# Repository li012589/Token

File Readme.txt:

Welcome to JRT token project!!

			   This is a readme file

				Ver. Alpha

		   ***************************************

For eagle schematic and borad files go to Hardware, schematic files are ended with .sch while borad files are ended with .brd 
For hardware document, go to /Hardware/document

For software, go to /Software
For information (e.g. todo list) about software, go to /Software/document

Enjoy your day!

		   ****************************************

Known Bugs:

		   ****************************************
Hosted By Li S.H.@li012589li@163.com  
	  Lv Y.X.@376324017@qq.com

locate at JinLin Univ. robot team Jinlin University,South QianWei ChangChun 	  	          Jilin Prov. China

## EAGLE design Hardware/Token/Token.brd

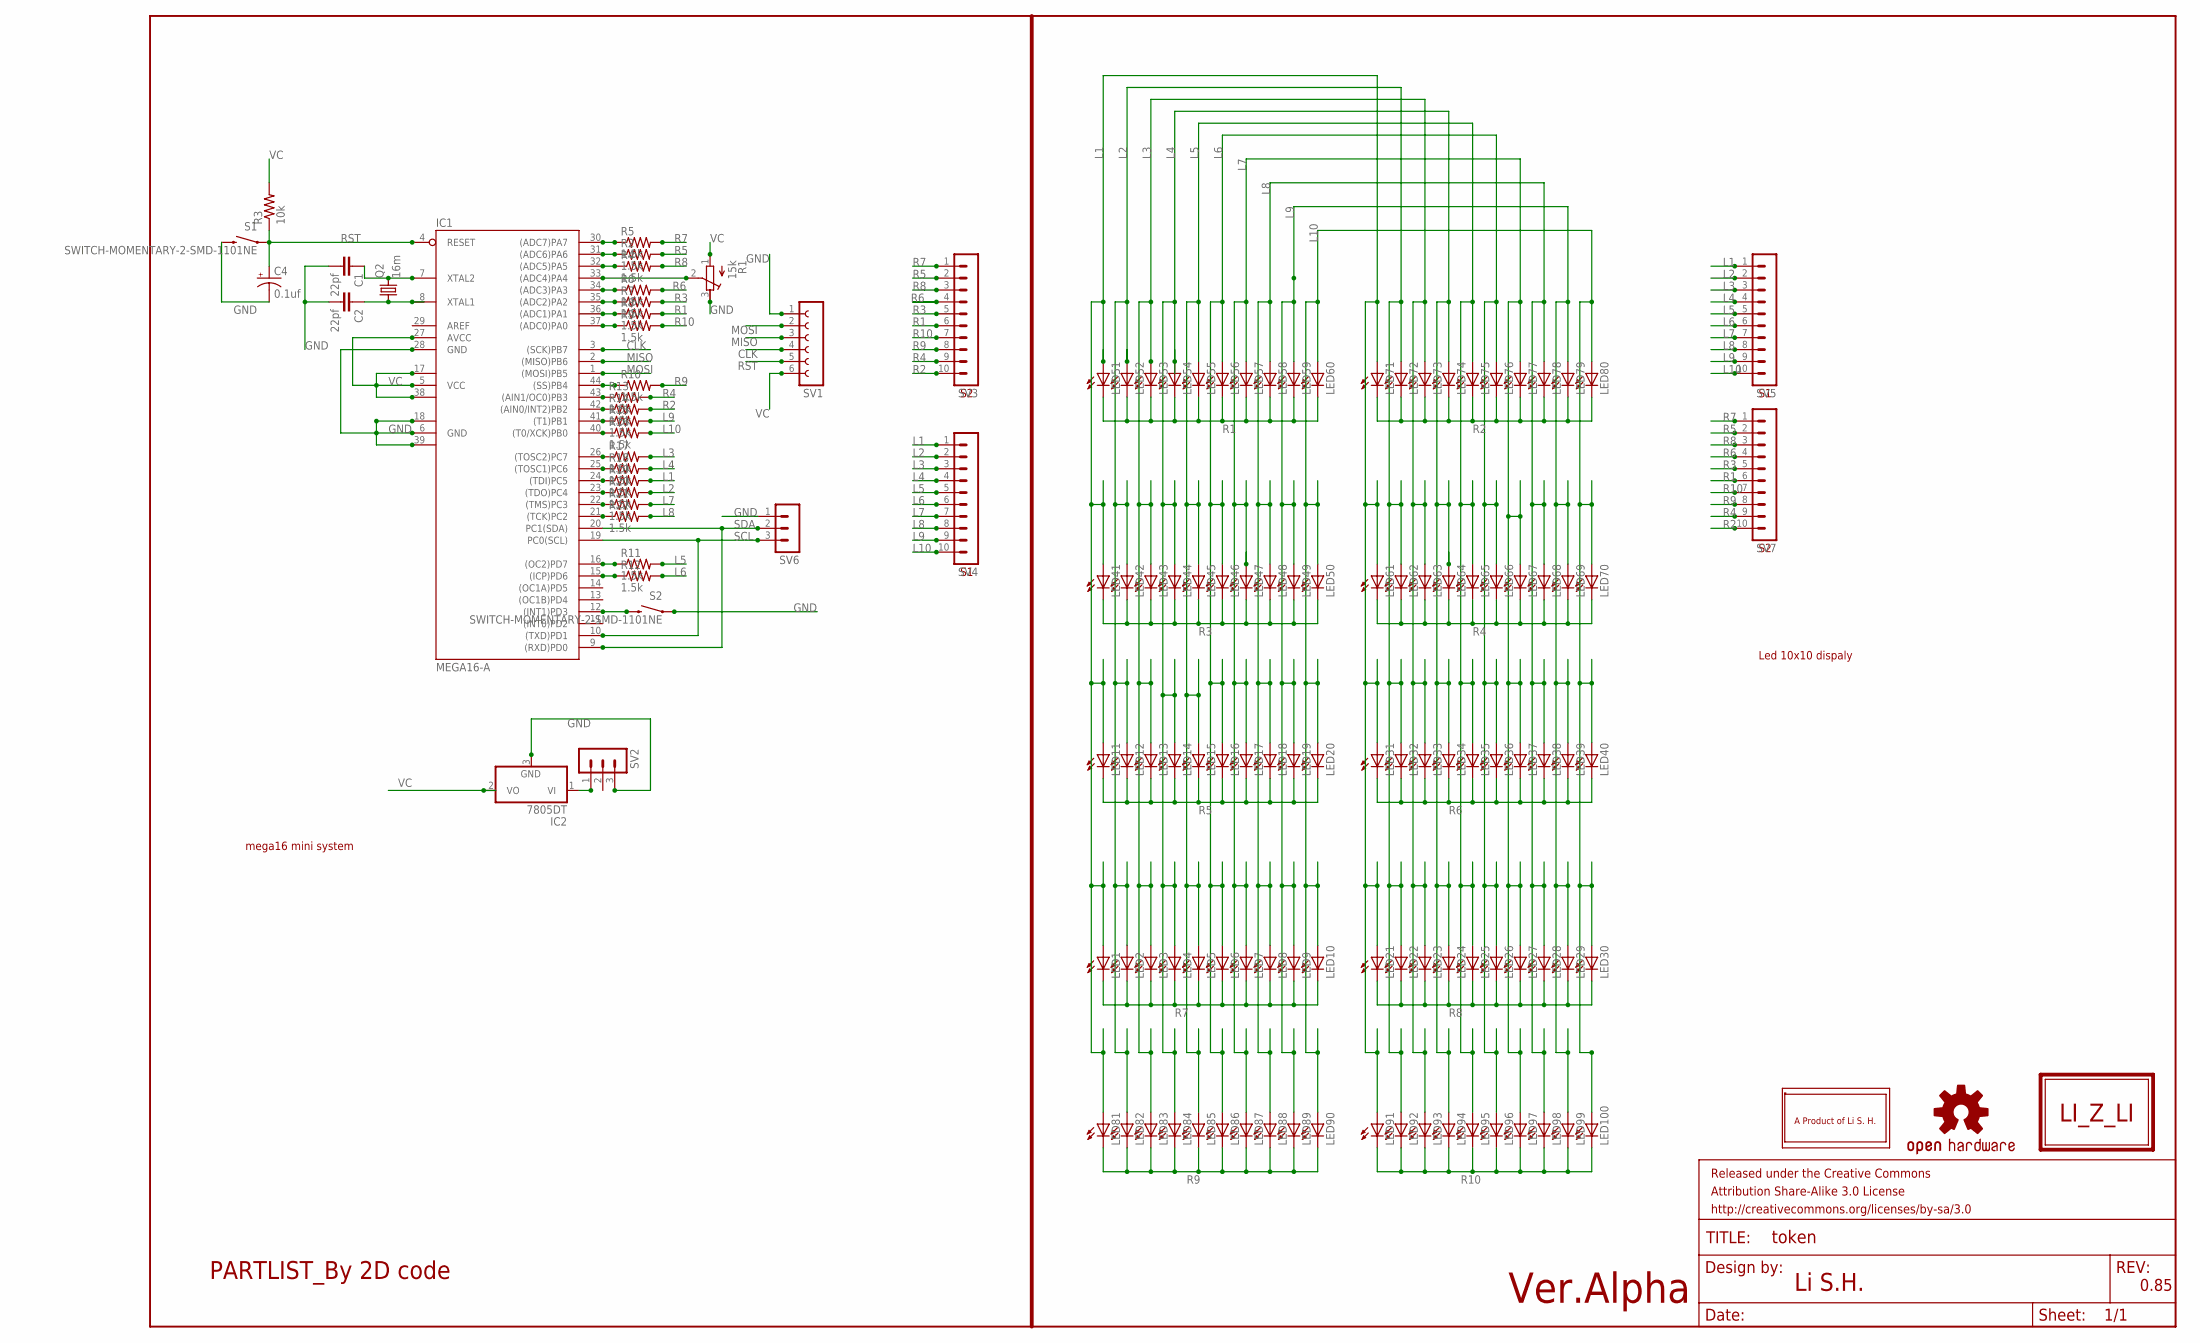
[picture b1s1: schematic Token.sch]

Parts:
C1, C2: 22pf; C0402
C4: 0.1uf; D/7343-31W
FRAME1: FRAME-LEDGER; CREATIVE_COMMONS
IC1: MEGA16-A; TQFP44
IC2: 7805DT; TO252
LED1, LED2, LED3, LED4, LED5, LED6, LED7, LED8, LED9, LED10, LED11, LED12, LED13, LED14, LED15, LED16, LED17, LED18, LED19, LED20, LED21, LED22, LED23, LED24, LED25, LED26, LED27, LED28, LED29, LED30, LED31, LED32, LED33, LED34, LED35, LED36, LED37, LED38, LED39, LED40, LED41, LED42, LED43, LED44, LED45, LED46, LED47, LED48, LED49, LED50, LED51, LED52, LED53, LED54, LED55, LED56, LED57, LED58, LED59, LED60, LED61, LED62, LED63, LED64, LED65, LED66, LED67, LED68, LED69, LED70, LED71, LED72, LED73, LED74, LED75, LED76, LED77, LED78, LED79, LED80, LED81, LED82, LED83, LED84, LED85, LED86, LED87, LED88, LED89, LED90, LED91, LED92, LED93, LED94, LED95, LED96, LED97, LED98, LED99, LED100: LEDCHIPLED_0805; CHIPLED_0805
LOGO1: OSHW-LOGOS; OSHW-LOGO-S
Q2: 16m; HC49UP
R1: 15k; RTRIM64W
R2, R4, R5, R6, R7, R8, R9, R10, R11, R12, R13, R14, R15, R16, R17, R18, R19, R20, R21, R22: 1.5k; R0201
R3: 10k; R0201
S1, S2: SWITCH-MOMENTARY-2-SMD-1101NE; TACTILE-SWITCH-1101NE
SV1: FE06-1; FE06
SV2, SV6: MA03-1
SV3, SV4, SV5, SV7: MA10-1
U$1: NO1
U$2: NO2
U$3: VERALPHA
U$4: PARTIST-2DCODE; PARTLIST-2DCODE

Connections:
CLK: IC1.3 ((SCK)PB7), SV1.4
GND: C1.2, C2.2, C4.-, IC1.6 (GND), IC1.18 (GND1), IC1.28 (GND), IC1.39 (GND2), IC2.3 (GND), R1.3 (A), S1.P$2 (2), S2.P$1 (1), SV1.1, SV2.3, SV6.1
L1: LED1.A, LED11.A, LED21.A, LED31.A, LED41.A, LED51.A, LED61.A, LED71.A, LED81.A, LED91.A, SV5.1
L2: LED2.A, LED12.A, LED22.A, LED32.A, LED42.A, LED52.A, LED62.A, LED72.A, LED82.A, LED92.A, SV5.2
L3: LED3.A, LED13.A, LED23.A, LED33.A, LED43.A, LED53.A, LED63.A, LED73.A, LED83.A, LED93.A, SV5.3
L4: LED4.A, LED14.A, LED24.A, LED34.A, LED44.A, LED54.A, LED64.A, LED74.A, LED84.A, LED94.A, SV5.4
L5: LED5.A, LED15.A, LED25.A, LED35.A, LED45.A, LED55.A, LED65.A, LED75.A, LED85.A, LED95.A, SV5.5
L6: LED6.A, LED16.A, LED26.A, LED36.A, LED46.A, LED56.A, LED66.A, LED76.A, LED86.A, LED96.A, SV5.6
L7: LED7.A, LED17.A, LED27.A, LED37.A, LED47.A, LED57.A, LED67.A, LED77.A, LED87.A, LED97.A, SV5.7
L8: LED8.A, LED18.A, LED28.A, LED38.A, LED48.A, LED58.A, LED68.A, LED78.A, LED88.A, LED98.A, SV5.8
L9: LED9.A, LED19.A, LED29.A, LED39.A, LED49.A, LED59.A, LED69.A, LED79.A, LED89.A, LED99.A, SV5.9
L10: LED10.A, LED20.A, LED30.A, LED40.A, LED50.A, LED60.A, LED70.A, LED80.A, LED90.A, LED100.A, SV5.10
MISO: IC1.2 ((MISO)PB6), SV1.3
MOSI: IC1.1 ((MOSI)PB5), SV1.2
unnamed: IC1.30 ((ADC7)PA7), R5.1
unnamed: IC1.43 ((AIN1/OC0)PB3), R13.1
unnamed: IC1.42 ((AIN0/INT2)PB2), R14.1
unnamed: IC1.41 ((T1)PB1), R15.1
unnamed: IC1.31 ((ADC6)PA6), R2.1
unnamed: IC1.32 ((ADC5)PA5), R4.1
unnamed: IC1.33 ((ADC4)PA4), R1.2 (S)
unnamed: IC1.34 ((ADC3)PA3), R6.1
unnamed: C2.1, IC1.8 (XTAL1), Q2.1
unnamed: C1.1, IC1.7 (XTAL2), Q2.2
unnamed: IC1.35 ((ADC2)PA2), R7.1
unnamed: IC1.36 ((ADC1)PA1), R8.1
unnamed: IC2.1 (VI), SV2.1
unnamed: IC1.37 ((ADC0)PA0), R9.1
unnamed: IC1.12 ((INT1)PD3), S2.P$2 (2)
unnamed: IC1.44 ((SS)PB4), R10.1
unnamed: IC1.16 ((OC2)PD7), R11.1
unnamed: IC1.15 ((ICP)PD6), R12.1
unnamed: IC1.40 ((T0/XCK)PB0), R16.1
unnamed: IC1.26 ((TOSC2)PC7), R17.1
unnamed: IC1.25 ((TOSC1)PC6), R18.1
unnamed: IC1.24 ((TDI)PC5), R19.1
unnamed: IC1.23 ((TDO)PC4), R20.1
unnamed: IC1.22 ((TMS)PC3), R21.1
unnamed: IC1.21 ((TCK)PC2), R22.1
unnamed: R5.2, SV3.1
unnamed: R2.2, SV3.2
unnamed: R4.2, SV3.3
unnamed: R6.2, SV3.4
unnamed: R7.2, SV3.5
unnamed: R8.2, SV3.6
unnamed: R9.2, SV3.7
unnamed: R10.2, SV3.8
unnamed: R13.2, SV3.9
unnamed: R14.2, SV3.10
unnamed: R15.2, SV4.9
unnamed: R16.2, SV4.10
unnamed: R17.2, SV4.3
unnamed: R18.2, SV4.4
unnamed: R19.2, SV4.1
unnamed: R20.2, SV4.2
unnamed: R21.2, SV4.7
unnamed: R22.2, SV4.8
unnamed: R11.2, SV4.5
unnamed: R12.2, SV4.6
R1: LED51.C, LED52.C, LED53.C, LED54.C, LED55.C, LED56.C, LED57.C, LED58.C, LED59.C, LED60.C, SV7.6
R2: LED71.C, LED72.C, LED73.C, LED74.C, LED75.C, LED76.C, LED77.C, LED78.C, LED79.C, LED80.C, SV7.10
R3: LED41.C, LED42.C, LED43.C, LED44.C, LED45.C, LED46.C, LED47.C, LED48.C, LED49.C, LED50.C, SV7.5
R4: LED61.C, LED62.C, LED63.C, LED64.C, LED65.C, LED66.C, LED67.C, LED68.C, LED69.C, LED70.C, SV7.9
R5: LED11.C, LED12.C, LED13.C, LED14.C, LED15.C, LED16.C, LED17.C, LED18.C, LED19.C, LED20.C, SV7.2
R6: LED31.C, LED32.C, LED33.C, LED34.C, LED35.C, LED36.C, LED37.C, LED38.C, LED39.C, LED40.C, SV7.4
R7: LED1.C, LED2.C, LED3.C, LED4.C, LED5.C, LED6.C, LED7.C, LED8.C, LED9.C, LED10.C, SV7.1
R8: LED21.C, LED22.C, LED23.C, LED24.C, LED25.C, LED26.C, LED27.C, LED28.C, LED29.C, LED30.C, SV7.3
R9: LED81.C, LED82.C, LED83.C, LED84.C, LED85.C, LED86.C, LED87.C, LED88.C, LED89.C, LED90.C, SV7.8
R10: LED91.C, LED92.C, LED93.C, LED94.C, LED95.C, LED96.C, LED97.C, LED98.C, LED99.C, LED100.C, SV7.7
RST: C4.+, IC1.4 (RESET), R3.1, S1.P$1 (1), SV1.5
SCL: IC1.10 ((TXD)PD1), IC1.19 (PC0(SCL)), SV6.3
SDA: IC1.9 ((RXD)PD0), IC1.20 (PC1(SDA)), SV6.2
VC: IC1.5 (VCC), IC1.17 (VCC1), IC1.27 (AVCC), IC1.38 (VCC2), IC2.2 (VO), R1.1 (E), R3.2, SV1.6

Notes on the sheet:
Li S.H.
0.85
mega16 mini system
Led 10x10 dispaly

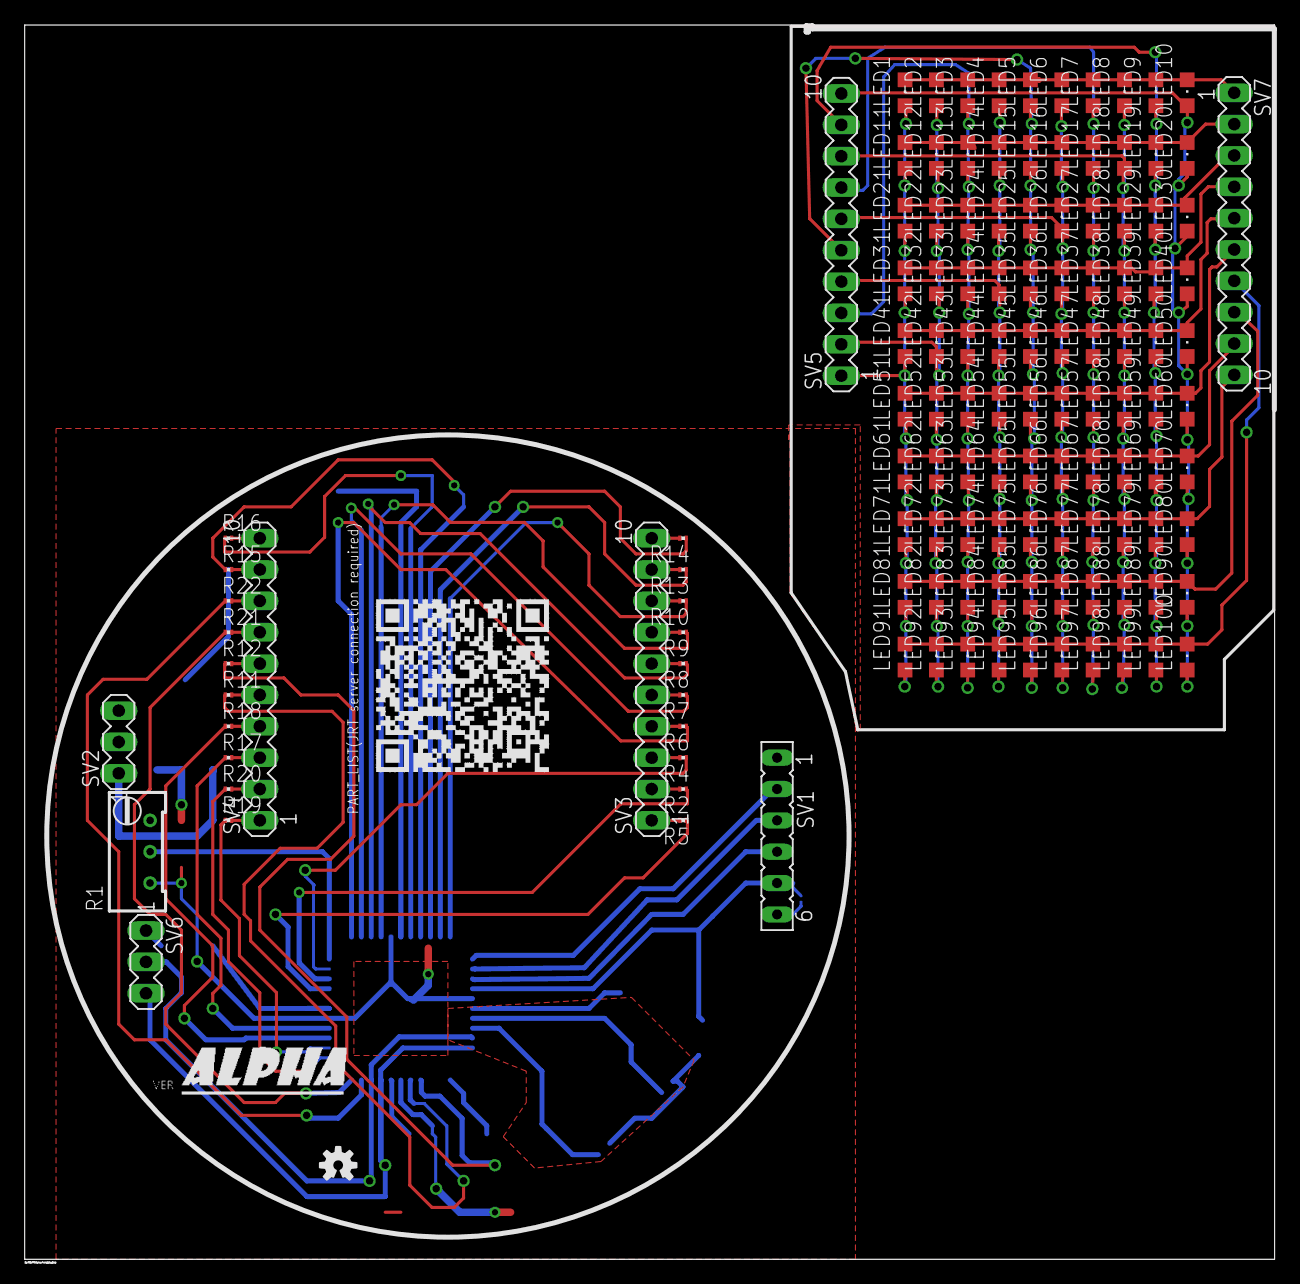
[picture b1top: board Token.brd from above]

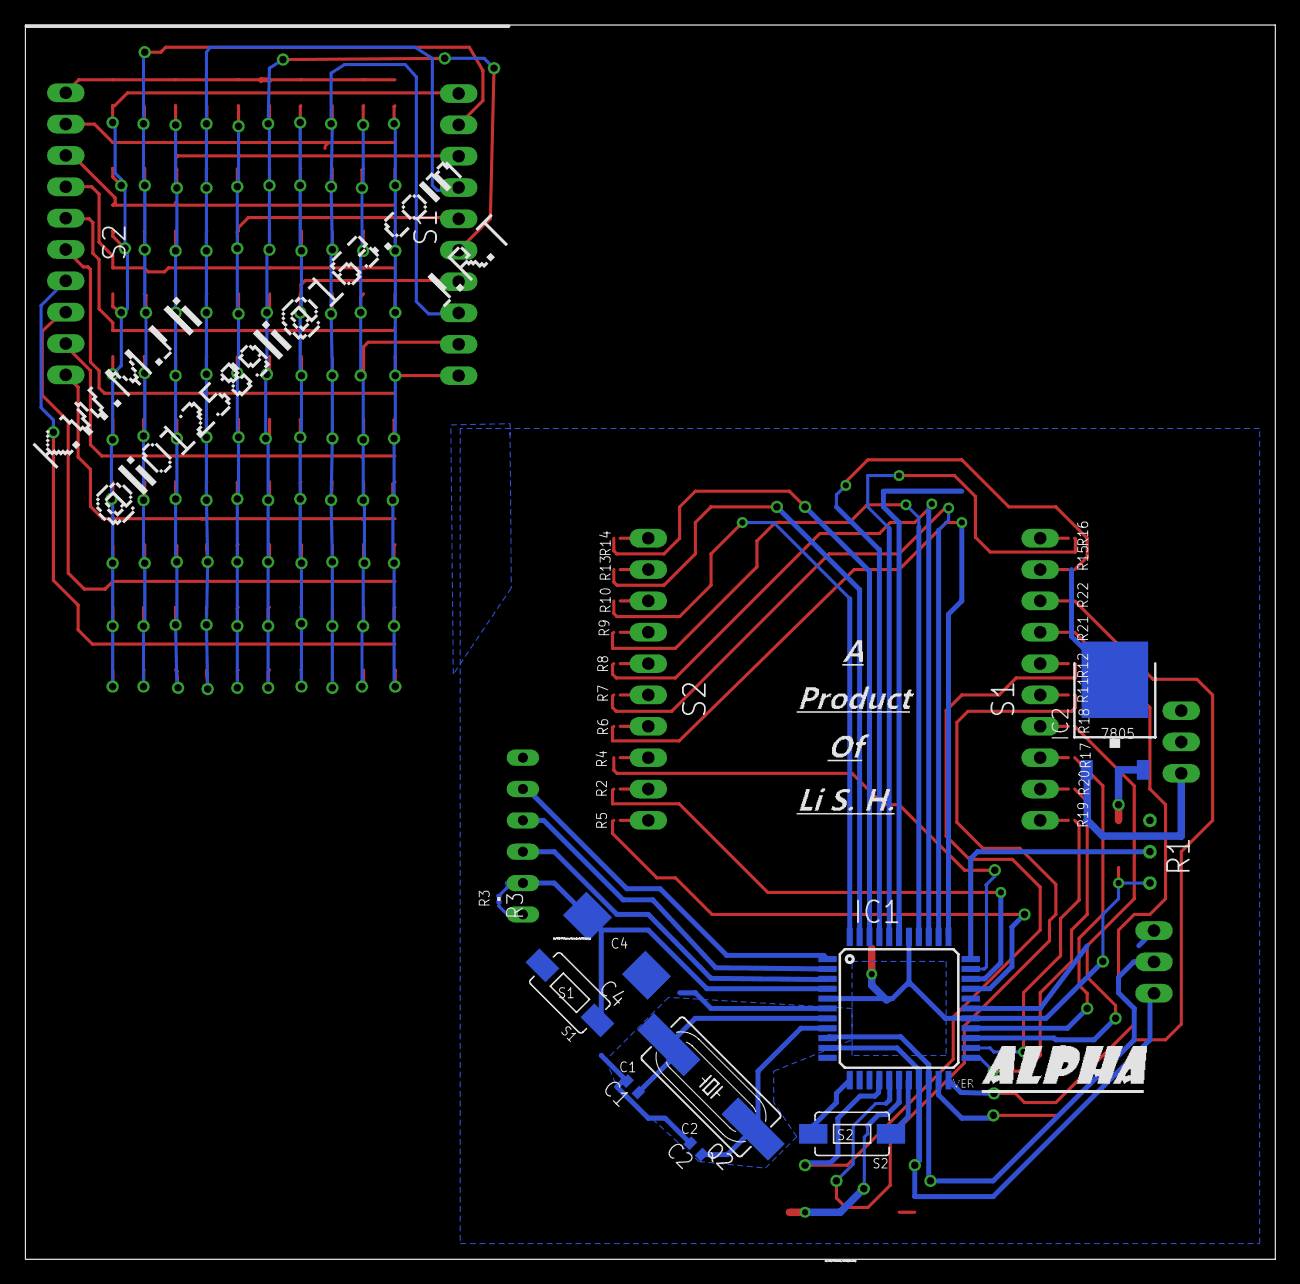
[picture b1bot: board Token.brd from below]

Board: 2 copper layers, 101.1 x 99.8 mm, 143 parts (13 on the bottom side), 73 nets.

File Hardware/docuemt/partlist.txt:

Part     Value                         Device                        Package               Library                    Sheet

C1       22pf                          CC0402                        C0402                 eagle-ltspice              1
C2       22pf                          CC0402                        C0402                 eagle-ltspice              1
C4       0.1uf                         CPOL-USD/7343-31W             D/7343-31W            adafruit                   1
IC1      MEGA16-A                      MEGA16-A                      TQFP44                atmel                      1
IC2      7805DT                        7805DT                        TO252                 adafruit                   1
LED1                                   LEDCHIPLED_0805               CHIPLED_0805          led                        1
.........
LED100                                 LEDCHIPLED_0805               CHIPLED_0805          led                        1
Q2       16m                           CRYSTALHC49UP                 HC49UP                crystal                    1
R3       10k                           R-US_R0201                    R0201                 rcl                        1
R1       15k                           R-TRIMM64W                    RTRIM64W              resistor                   1
R2       1.5k                          R-US_R0201                    R0201                 rcl                        1
......(except R3 !!!)
R22      1.5k                          R-US_R0201                    R0201                 rcl                        1
S1       SWITCH-MOMENTARY-2-SMD-1101NE SWITCH-MOMENTARY-2-SMD-1101NE TACTILE-SWITCH-1101NE SparkFun-Electromechanical 1
S2       SWITCH-MOMENTARY-2-SMD-1101NE SWITCH-MOMENTARY-2-SMD-1101NE TACTILE-SWITCH-1101NE SparkFun-Electromechanical 1

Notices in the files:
parts and their libraries:
SparkFun-Aesthetics: Licensing: CC v3.0 Share-Alike You are welcome to use this library for commercial purposes.
SparkFun-Aesthetics: Released under the Creative Commons Attribution Share-Alike 3.0 License
SparkFun-Aesthetics: http://creativecommons.org/licenses/by-sa/3.0
